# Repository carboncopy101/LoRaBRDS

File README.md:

# LoRa Boards

## Overview

This repository contains multiple iteration 
of expansion transceiver boards for the Raspberry Pi and Jetson Nano.

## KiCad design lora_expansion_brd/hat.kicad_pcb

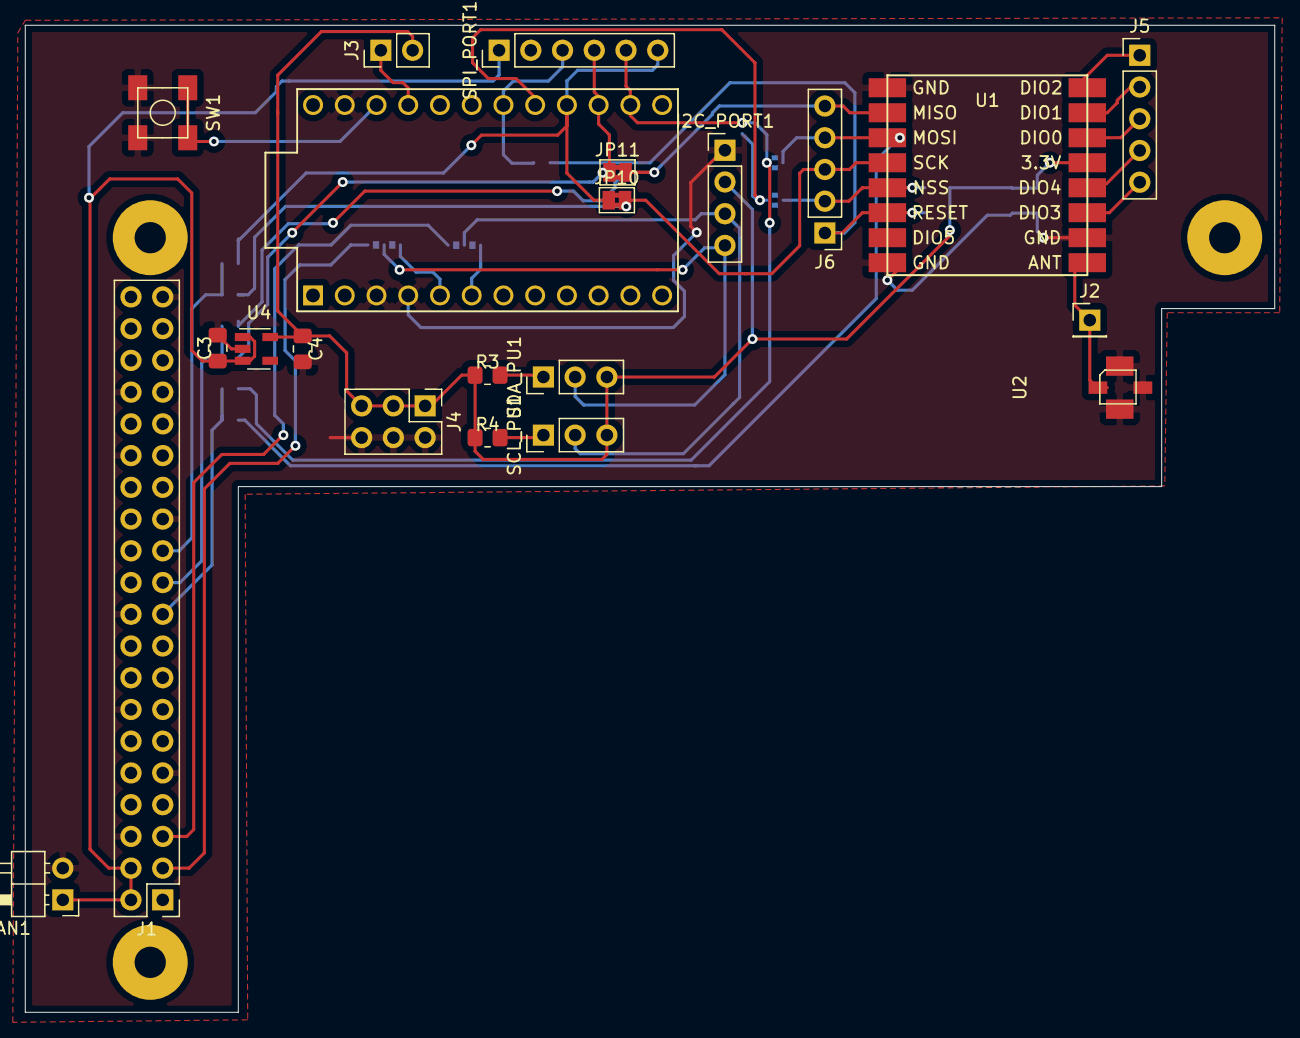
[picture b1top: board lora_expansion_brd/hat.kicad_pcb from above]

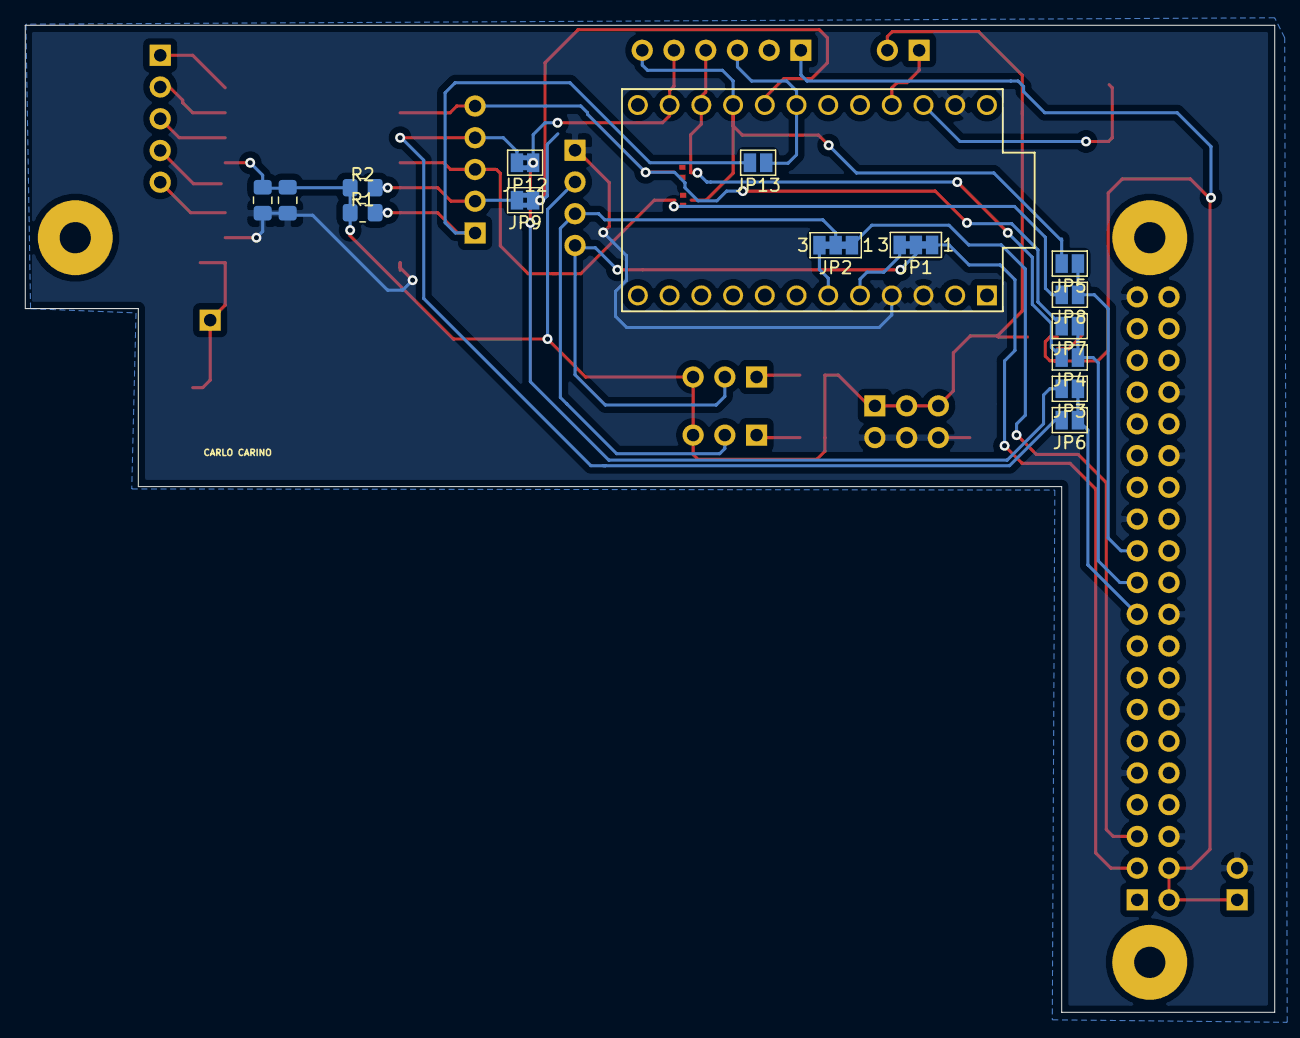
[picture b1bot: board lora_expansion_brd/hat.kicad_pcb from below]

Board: 2 copper layers, 100.0 x 79.0 mm, 40 parts (15 on the bottom side), 33 nets.

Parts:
C1, C3, C4: 10u; C_0805_2012Metric_Pad1.18x1.45mm_HandSolder
C2: 0.1u; C_0805_2012Metric_Pad1.18x1.45mm_HandSolder
FAN1: Conn_01x02_Male; PinHeader_1x02_P2.54mm_Horizontal
H1, H2, H3: MountingHole_Pad; jetson_nano_mounting
I2C_PORT1: Conn_01x04_Male; PinHeader_1x04_P2.54mm_Vertical
J1: GPIO; PinHeader_2x20_P2.54mm_Vertical
J2: Conn_01x01_Male; PinHeader_1x01_P2.54mm_Vertical
J3: Conn_01x02_Male; PinHeader_1x02_P2.54mm_Vertical
J4: Conn_02x03_Odd_Even; PinHeader_2x03_P2.54mm_Vertical
J5, J6: Conn_01x05_Male; PinHeader_1x05_P2.54mm_Vertical
JP1, JP2: SolderJumper_3_Bridged123; SolderJumper-3_P1.3mm_Bridged12_Pad1.0x1.5mm_NumberLabels
JP3, JP4, JP5, JP6, JP7, JP8, JP13: SolderJumper_2_Open; SolderJumper-2_P1.3mm_Open_Pad1.0x1.5mm
JP9, JP10, JP11, JP12: SolderJumper_2_Bridged; SolderJumper-2_P1.3mm_Bridged2Bar_Pad1.0x1.5mm
R1, R2: 10k; R_0805_2012Metric_Pad1.20x1.40mm_HandSolder
R3, R4: 4.7k; R_0805_2012Metric_Pad1.20x1.40mm_HandSolder
SCL_PU1: Conn_01x03_Male; PinHeader_1x03_P2.54mm_Vertical
SDA_PU1: Conn_01x03_Male; PinHeader_1x03_P2.54mm_Vertical
SPI_PORT1: Conn_01x06_Male; PinHeader_1x06_P2.54mm_Vertical
SW1: SW_Push; smd_tact_switch
U1: RFM95; RFM95-Headers
U2: uFL-SMA; uFLSMA
U3: ProMicro
U4: AP2112K-3.3; SOT-23-5

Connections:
3.3V: C1.1, C2.1, C4.1, I2C_PORT1.2, J3.2, J4.1, J4.3, J4.5, R1.1, R2.1, R3.1, R4.1, SCL_PU1.3, SDA_PU1.3, U1.13, U4.5
5V: C3.1, FAN1.1, J1.2, J1.4, SPI_PORT1.1, U4.1, U4.3
/DIO0: J5.3, U1.14
/DIO1: J5.2, U1.15
/DIO2: J5.1, U1.16
/DIO3: J5.5, U1.11
/DIO4: J5.4, U1.12
/MCU_3.3V: J3.1, U3.21
/MCU_CS: JP9.1, U3.17
/MCU_MISO: JP4.2, JP11.1, SPI_PORT1.4, U3.15
/MCU_MOSI: JP3.2, JP12.1, SPI_PORT1.5, U3.14
/MCU_SCK: JP5.2, JP10.1, SPI_PORT1.6, U3.16
/MCU_SCL: JP2.3, U3.6
/MCU_SDA: JP1.3, U3.5
/OPT_RST: JP13.1, SPI_PORT1.3, U3.18
/PI_3.3V: J1.1, J1.17
/PI_MISO: J1.21, JP4.1, JP7.1
/PI_MOSI: J1.19, JP3.1, JP6.1
/PI_SCK: J1.23, JP5.1, JP8.1
/PI_SCL: J1.5, JP2.1
/PI_SDA: J1.3, JP1.1
/RFM_CS: J6.2, JP9.2, R2.2, U1.5
/RFM_MISO: J6.5, JP7.2, JP11.2, U1.2
/RFM_MOSI: J6.4, JP6.2, JP12.2, U1.3
/RFM_RST: J6.1, JP13.2, R1.2, U1.6
/RFM_SCK: J6.3, JP8.2, JP10.2, U1.4
/SCL: I2C_PORT1.3, JP2.2, SCL_PU1.2
/SDA: I2C_PORT1.4, JP1.2, SDA_PU1.2
GND: C1.2, C2.2, C3.2, C4.2, FAN1.2, I2C_PORT1.1, J1.6, J1.9, J1.14, J1.20, J1.25, J1.30, J1.34, J1.39, J4.2, J4.4, J4.6, SW1.2, U1.1, U1.8, U1.10, U2.2, U2.3, U2.4, U3.3, U3.4, U3.23, U4.2
unnamed: J2.1, U1.9, U2.1
unnamed: R3.2, SDA_PU1.1
unnamed: R4.2, SCL_PU1.1
unnamed: SW1.1, U3.22

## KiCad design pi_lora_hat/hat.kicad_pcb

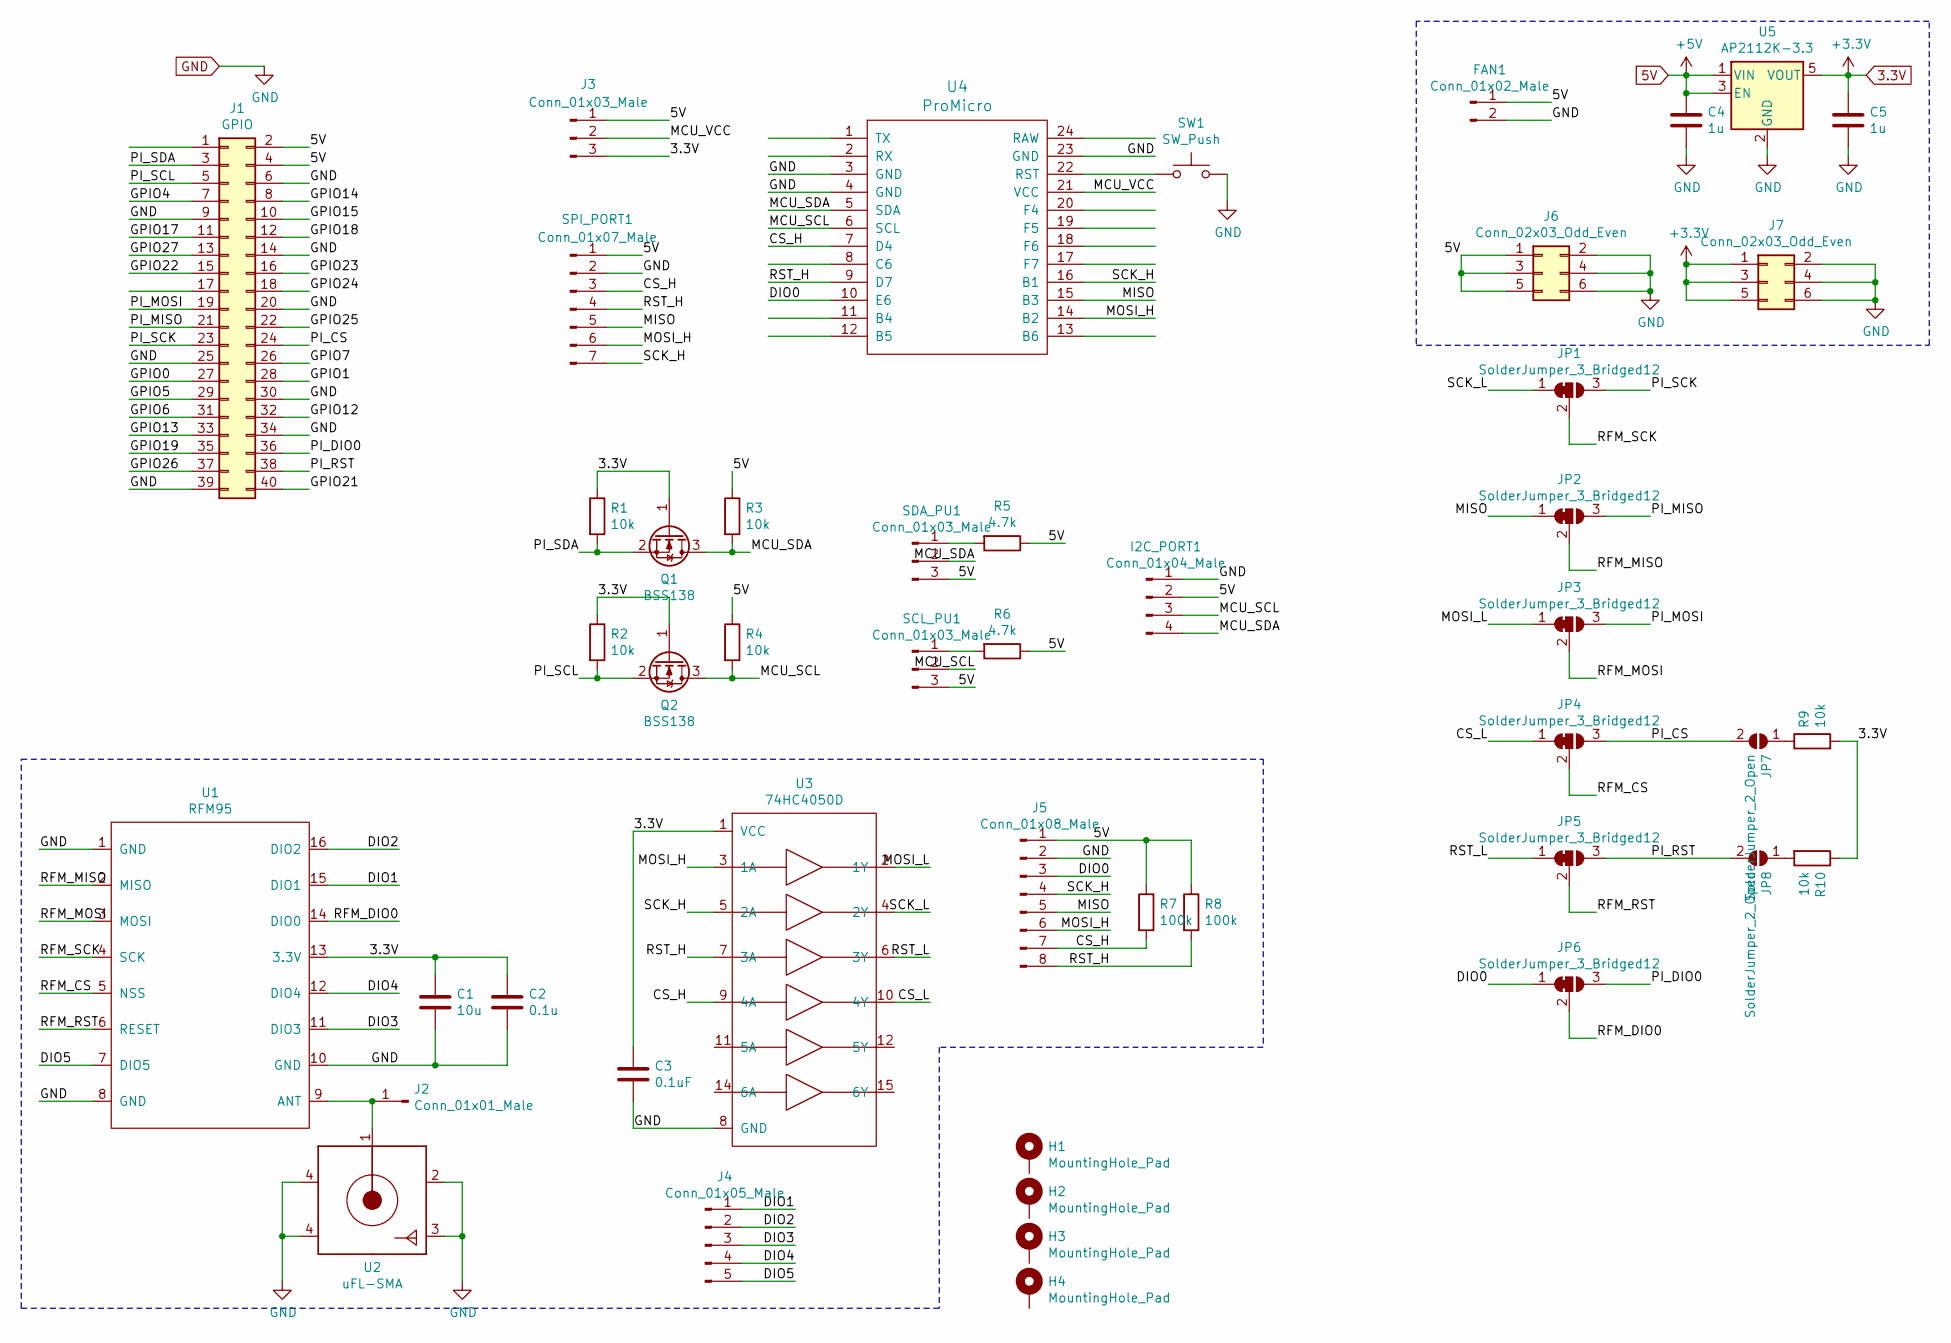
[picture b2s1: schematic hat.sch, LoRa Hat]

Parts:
C1: 10u; C_0805_2012Metric_Pad1.18x1.45mm_HandSolder
C2: 0.1u; C_0805_2012Metric_Pad1.18x1.45mm_HandSolder
C3: 0.1uF; C_0805_2012Metric_Pad1.18x1.45mm_HandSolder
C4, C5: 1u; C_0805_2012Metric_Pad1.18x1.45mm_HandSolder
FAN1: Conn_01x02_Male; PinHeader_1x02_P2.54mm_Horizontal
H1, H2, H3, H4: MountingHole_Pad; pi_mounting_2.5_6
I2C_PORT1: Conn_01x04_Male; PinHeader_1x04_P2.54mm_Vertical
J1: GPIO; PinHeader_2x20_P2.54mm_Vertical
J2: Conn_01x01_Male; PinHeader_1x01_P2.54mm_Vertical
J3: Conn_01x03_Male; PinHeader_1x03_P2.54mm_Vertical
J4: Conn_01x05_Male; PinHeader_1x05_P2.54mm_Vertical
J5: Conn_01x08_Male; PinHeader_1x08_P2.54mm_Vertical
J6, J7: Conn_02x03_Odd_Even; PinHeader_2x03_P2.54mm_Vertical
JP1, JP2, JP3, JP4, JP5, JP6: SolderJumper_3_Bridged12; SolderJumper-3_P1.3mm_Bridged12_Pad1.0x1.5mm
JP7, JP8: SolderJumper_2_Open; SolderJumper-2_P1.3mm_Open_Pad1.0x1.5mm
Q1, Q2: BSS138; SOT-23
R1, R2, R3, R4, R9, R10: 10k; R_0805_2012Metric_Pad1.20x1.40mm_HandSolder
R5, R6: 4.7k; R_0805_2012Metric_Pad1.20x1.40mm_HandSolder
R7, R8: 100k; R_0805_2012Metric_Pad1.20x1.40mm_HandSolder
SCL_PU1: Conn_01x03_Male; PinHeader_1x03_P2.54mm_Vertical
SDA_PU1: Conn_01x03_Male; PinHeader_1x03_P2.54mm_Vertical
SPI_PORT1: Conn_01x07_Male; PinHeader_1x07_P2.54mm_Vertical
SW1: SW_Push; SW_Push_1P1T_NO_6x6mm_H9.5mm
U1: RFM95; RFM95-Headers
U2: uFL-SMA; uFLSMA
U3: 74HC4050D; 74HC4050
U4: ProMicro
U5: AP2112K-3.3; SOT-23-5

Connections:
3.3V: C1.1, C2.1, C3.1, C5.1, J3.3, J7.1, J7.3, J7.5, Q1.1 (G), Q2.1 (G), R1.1, R2.1, R9.2, R10.1, U1.13 (3.3V), U3.1 (VCC), U5.5 (VOUT)
5V: C4.1, FAN1.1, I2C_PORT1.2, J1.2, J1.4, J3.1, J5.1, J6.1, J6.3, J6.5, R3.1, R4.1, R5.1, R6.1, R7.1, R8.1, SCL_PU1.3, SDA_PU1.3, SPI_PORT1.1, U5.1 (VIN), U5.3 (EN)
/CS_H: J5.7, R7.2, SPI_PORT1.3, U3.9 (4A), U4.7 (D4)
/CS_L: JP4.1 (A), U3.10 (4Y)
/DIO0: J5.3, JP6.1 (A), U4.10 (E6)
/DIO1: J4.1, U1.15 (DIO1)
/DIO2: J4.2, U1.16 (DIO2)
/DIO3: J4.3, U1.11 (DIO3)
/DIO4: J4.4, U1.12 (DIO4)
/DIO5: J4.5, U1.7 (DIO5)
/GPIO0: J1.27
/GPIO1: J1.28
/GPIO4: J1.7
/GPIO5: J1.29
/GPIO6: J1.31
/GPIO7: J1.26
/GPIO12: J1.32
/GPIO13: J1.33
/GPIO14: J1.8
/GPIO15: J1.10
/GPIO17: J1.11
/GPIO18: J1.12
/GPIO19: J1.35
/GPIO21: J1.40
/GPIO22: J1.15
/GPIO23: J1.16
/GPIO24: J1.18
/GPIO25: J1.22
/GPIO26: J1.37
/GPIO27: J1.13
/MCU_SCL: I2C_PORT1.3, Q2.3 (D), R4.2, SCL_PU1.2, U4.6 (SCL)
/MCU_SDA: I2C_PORT1.4, Q1.3 (D), R3.2, SDA_PU1.2, U4.5 (SDA)
/MCU_VCC: J3.2, U4.21 (VCC)
/MISO: J5.5, JP2.1 (A), SPI_PORT1.5, U4.15 (B3)
/MOSI_H: J5.6, SPI_PORT1.6, U3.3 (1A), U4.14 (B2)
/MOSI_L: JP3.1 (A), U3.2 (1Y)
/PI_CS: J1.24, JP4.3 (B), JP7.2 (B)
/PI_DIO0: J1.36, JP6.3 (B)
/PI_MISO: J1.21, JP2.3 (B)
/PI_MOSI: J1.19, JP3.3 (B)
/PI_RST: J1.38, JP5.3 (B), JP8.2 (B)
/PI_SCK: J1.23, JP1.3 (B)
/PI_SCL: J1.5, Q2.2 (S), R2.2
/PI_SDA: J1.3, Q1.2 (S), R1.2
/RFM_CS: JP4.2 (C), U1.5 (NSS)
/RFM_DIO0: JP6.2 (C), U1.14 (DIO0)
/RFM_MISO: JP2.2 (C), U1.2 (MISO)
/RFM_MOSI: JP3.2 (C), U1.3 (MOSI)
/RFM_RST: JP5.2 (C), U1.6 (RESET)
/RFM_SCK: JP1.2 (C), U1.4 (SCK)
/RST_H: J5.8, R8.2, SPI_PORT1.4, U3.7 (3A), U4.9 (D7)
/RST_L: JP5.1 (A), U3.6 (3Y)
/SCK_H: J5.4, SPI_PORT1.7, U3.5 (2A), U4.16 (B1)
/SCK_L: JP1.1 (A), U3.4 (2Y)
GND: C1.2, C2.2, C3.2, C4.2, C5.2, FAN1.2, I2C_PORT1.1, J1.6, J1.9, J1.14, J1.20, J1.25, J1.30, J1.34, J1.39, J5.2, J6.2, J6.4, J6.6, J7.2, J7.4, J7.6, SPI_PORT1.2, SW1.2, U1.1 (GND), U1.8 (GND), U1.10 (GND), U2.2, U2.3, U2.4, U3.8 (GND), U4.3 (GND), U4.4 (GND), U4.23 (GND), U5.2 (GND)
unnamed: J2.1, U1.9 (ANT), U2.1
unnamed: JP7.1 (A), R9.1
unnamed: JP8.1 (A), R10.2
unnamed: R5.2, SDA_PU1.1
unnamed: R6.2, SCL_PU1.1
unnamed: SW1.1, U4.22 (RST)

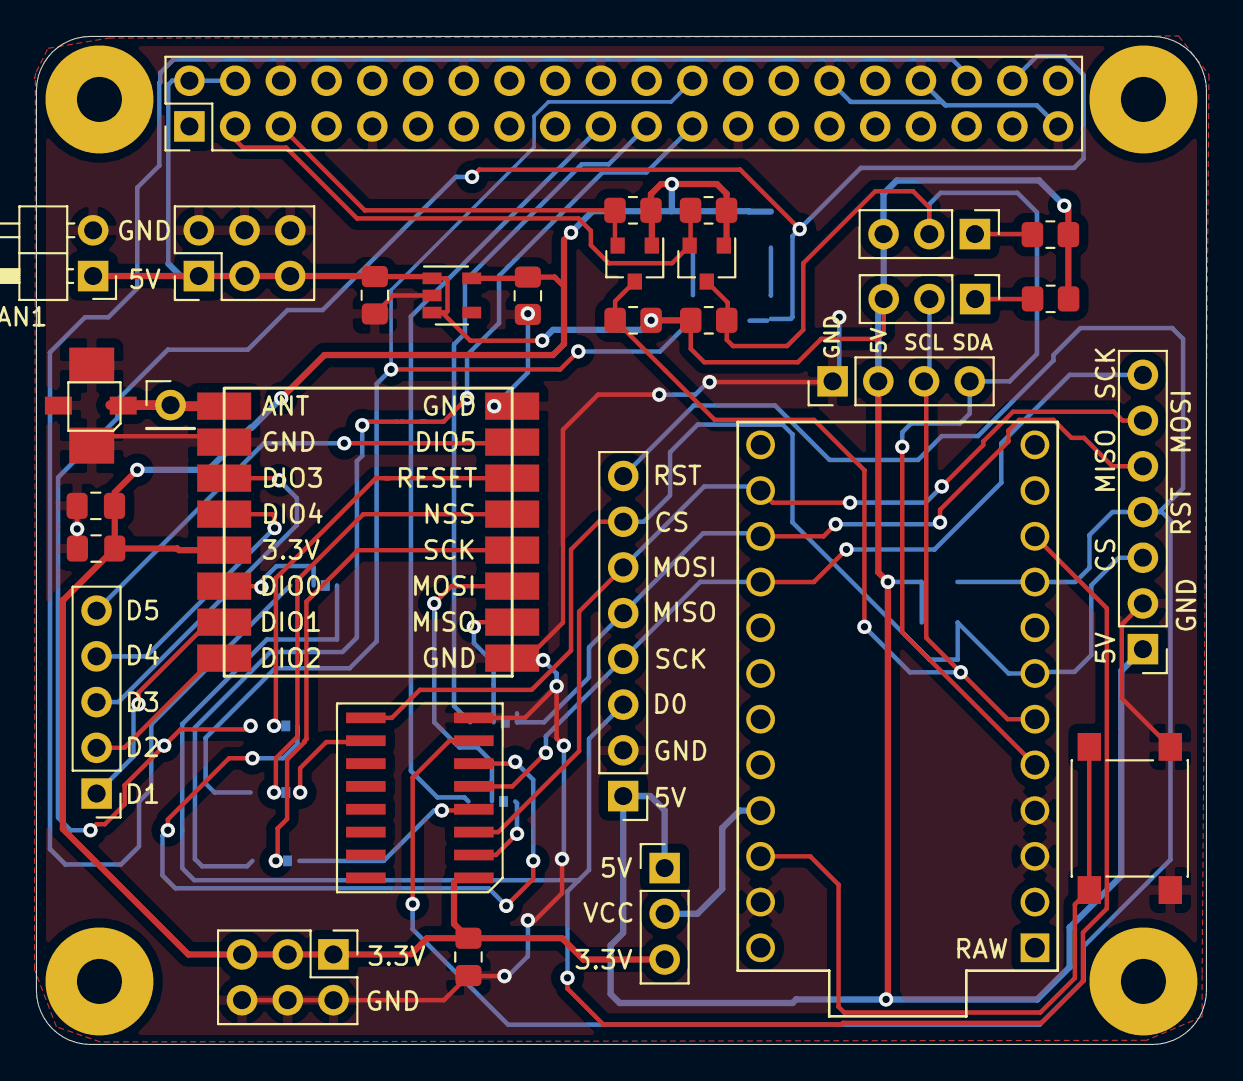
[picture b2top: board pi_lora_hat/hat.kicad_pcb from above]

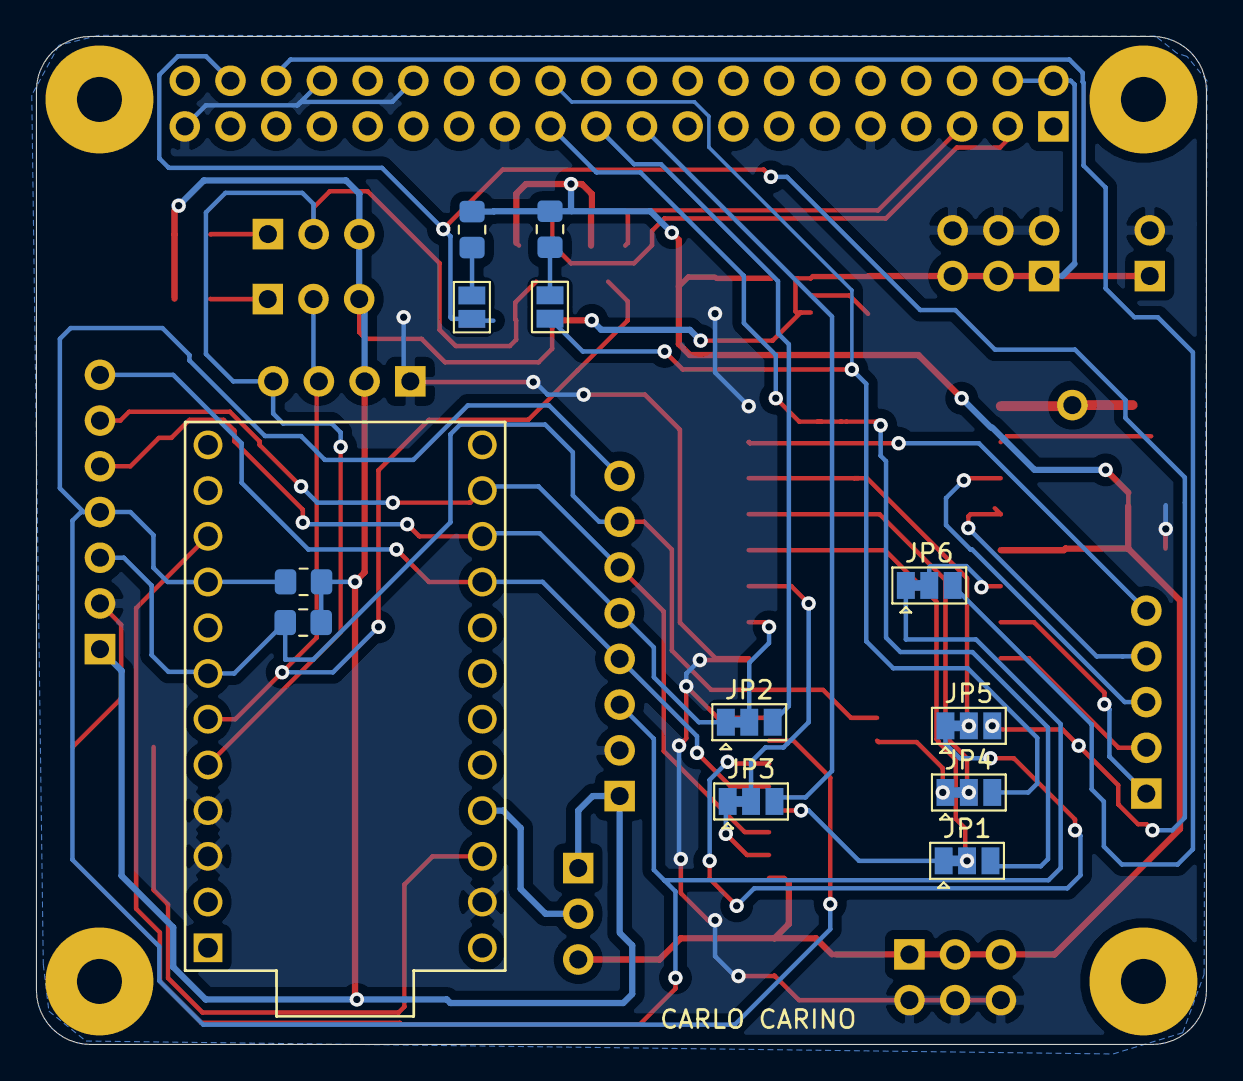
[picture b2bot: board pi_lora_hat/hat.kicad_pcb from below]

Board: 2 copper layers, 65.0 x 56.0 mm, 47 parts (12 on the bottom side), 41 nets.

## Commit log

2022-12-31 added 4 kicad files. 3 brds for rpi and 1 for jetson nano.
